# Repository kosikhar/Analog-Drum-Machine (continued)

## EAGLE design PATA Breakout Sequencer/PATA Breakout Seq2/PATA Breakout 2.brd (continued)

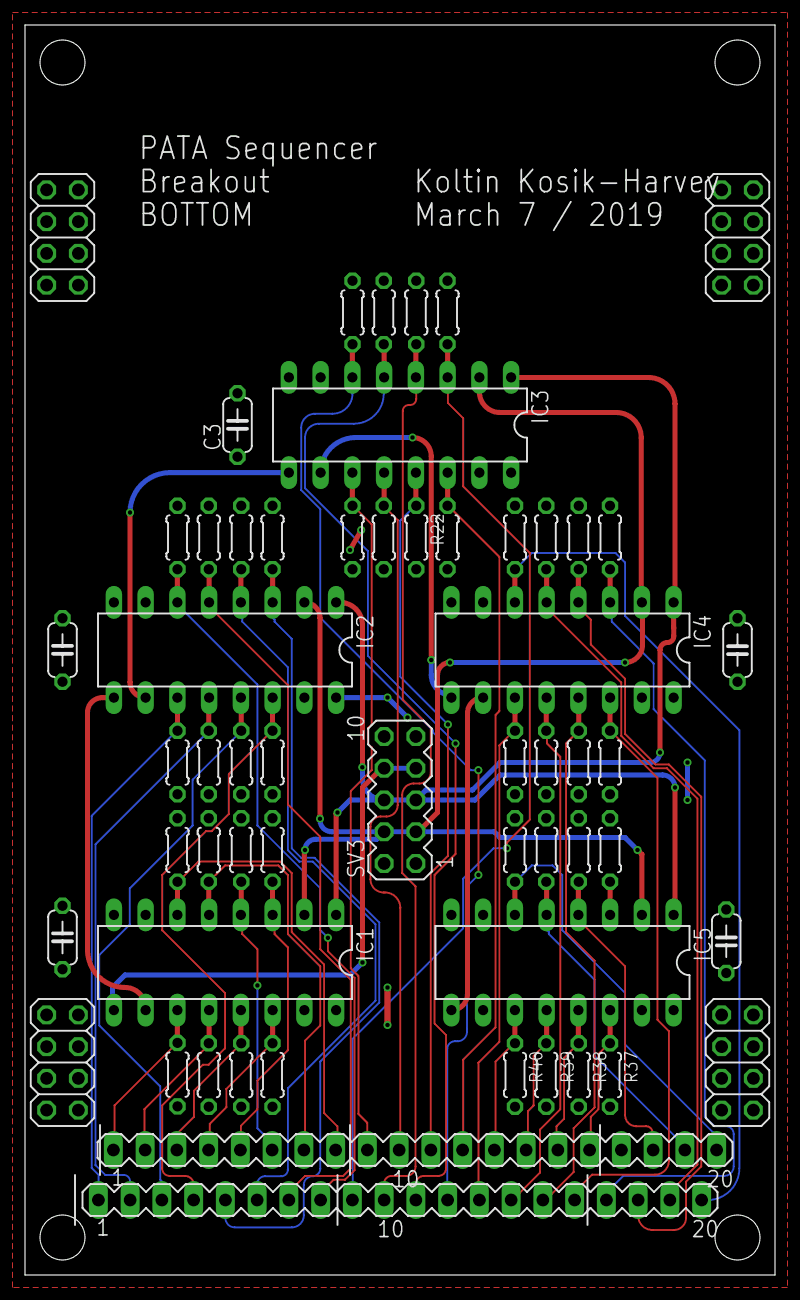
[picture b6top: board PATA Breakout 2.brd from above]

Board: 2 copper layers, 60.0 x 100.0 mm, 57 parts (0 on the bottom side), 49 nets.
